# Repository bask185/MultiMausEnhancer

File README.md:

# MultiMausEnhancer, makes the roco multimaus more user friendly

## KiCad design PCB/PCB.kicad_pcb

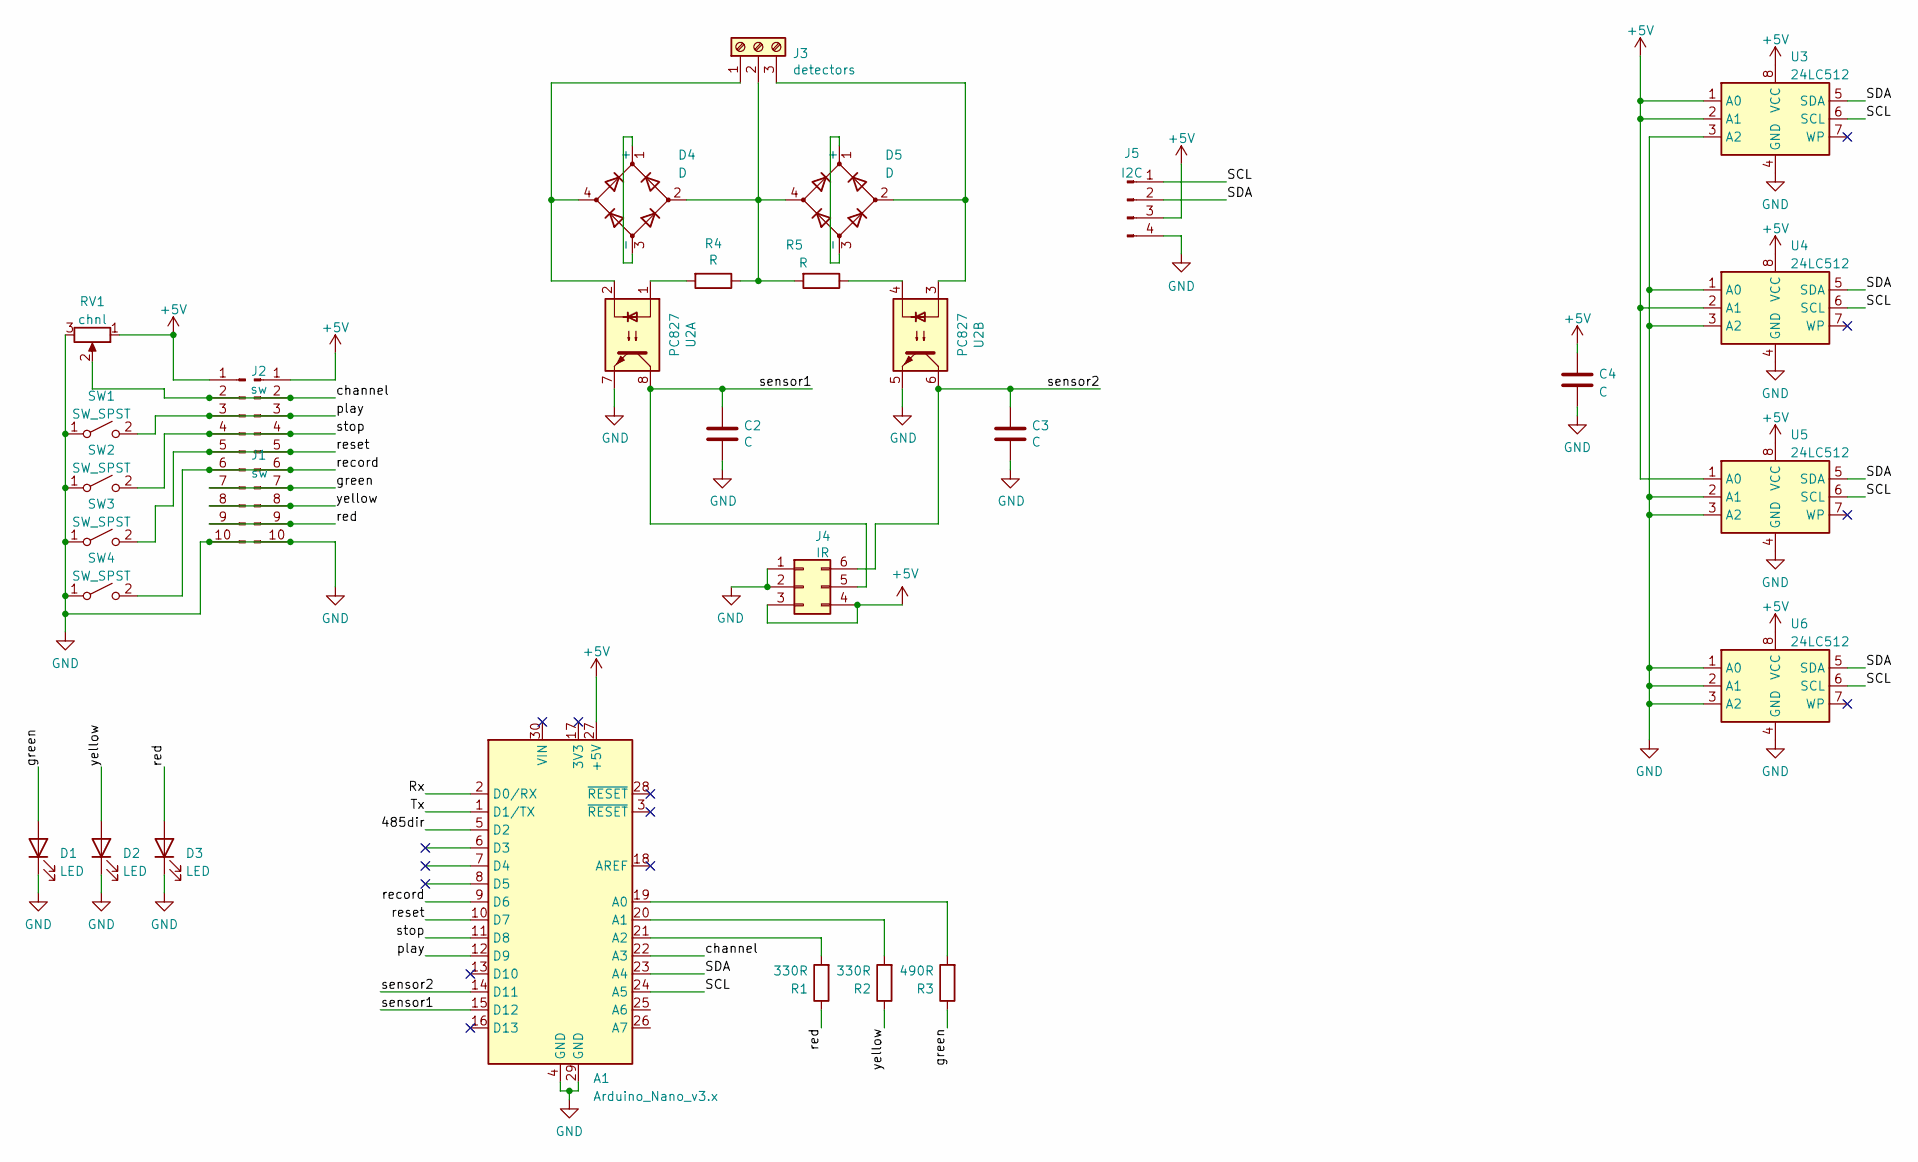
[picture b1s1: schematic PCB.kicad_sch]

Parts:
A1: Arduino_Nano_v3.x; Arduino_Nano
C2, C3, C4: C; C_Disc_D3.0mm_W1.6mm_P2.50mm
D1, D2, D3: LED; LED_D3.0mm
D4, D5: D; Diode_Bridge_Round_D9.0mm
J1, J2: sw; PinHeader_1x10_P2.54mm_Vertical
J3: detectors; TerminalBlock_Phoenix_MKDS-1,5-3-5.08_1x03_P5.08mm_Horizont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
J4: IR; PinHeader_2x03_P2.54mm_Vertical
J5: I2C; PinHeader_1x04_P2.54mm_Vertical
R1, R2: 330R; R_Axial_DIN0204_L3.6mm_D1.6mm_P7.62mm_Horizontal
R3: 490R; R_Axial_DIN0204_L3.6mm_D1.6mm_P7.62mm_Horizontal
R4, R5: R; R_Axial_DIN0204_L3.6mm_D1.6mm_P7.62mm_Horizontal
RV1: chnl; PinHeader_1x03_P2.54mm_Vertical
SW1, SW2, SW3, SW4: SW_SPST; SW_PUSH_6mm_H4.3mm
U2: PC827; DIP-8_W7.62mm
U3, U4, U5, U6: 24LC512; DIP-8_W7.62mm

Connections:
+5V: A1.27 (+5V), C4.1, J1.1, J2.1, J4.3, J4.4, J5.3, RV1.1, U3.1 (A0), U3.2 (A1), U3.8 (VCC), U4.2 (A1), U4.8 (VCC), U5.1 (A0), U5.8 (VCC), U6.8 (VCC)
/485dir: A1.5 (D2)
/Rx: A1.2 (D0/RX)
/SCL: A1.24 (A5), J5.1, U3.6 (SCL), U4.6 (SCL), U5.6 (SCL), U6.6 (SCL)
/SDA: A1.23 (A4), J5.2, U3.5 (SDA), U4.5 (SDA), U5.5 (SDA), U6.5 (SDA)
/Tx: A1.1 (D1/TX)
/channel: A1.22 (A3), J1.2, J2.2, RV1.2
/green: D1.2 (A), J1.7, J2.7, R3.1
/play: A1.12 (D9), J1.3, J2.3, SW1.2 (B)
/record: A1.9 (D6), J1.6, J2.6, SW4.2 (B)
/red: D3.2 (A), J1.9, J2.9, R1.1
/reset: A1.10 (D7), J1.5, J2.5, SW3.2 (B)
/sensor1: A1.15 (D12), C2.1, J4.5, U2.8
/sensor2: A1.14 (D11), C3.1, J4.6, U2.6
/stop: A1.11 (D8), J1.4, J2.4, SW2.2 (B)
/yellow: D2.2 (A), J1.8, J2.8, R2.1
GND: A1.4 (GND), A1.29 (GND), C2.2, C3.2, C4.2, D1.1 (K), D2.1 (K), D3.1 (K), J1.10, J2.10, J4.1, J4.2, J5.4, RV1.3, SW1.1 (A), SW2.1 (A), SW3.1 (A), SW4.1 (A), U2.5, U2.7, U3.3 (A2), U3.4 (GND), U4.1 (A0), U4.3 (A2), U4.4 (GND), U5.2 (A1), U5.3 (A2), U5.4 (GND), U6.1 (A0), U6.2 (A1), U6.3 (A2), U6.4 (GND)
unnamed: A1.19 (A0), R3.2
unnamed: A1.20 (A1), R2.2
unnamed: A1.21 (A2), R1.2
unnamed: D4.1 (+), D4.3 (-)
unnamed: D4.2, D5.4, J3.2, R4.1, R5.2
unnamed: D4.4, J3.1, U2.2
unnamed: D5.1 (+), D5.3 (-)
unnamed: D5.2, J3.3, U2.3
unnamed: R4.2, U2.1
unnamed: R5.1, U2.4

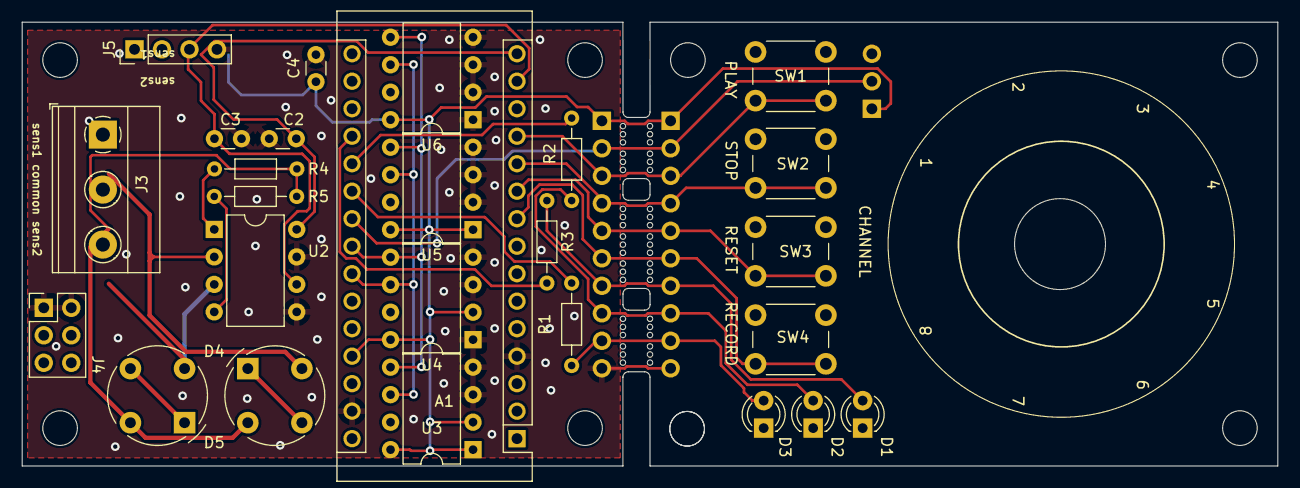
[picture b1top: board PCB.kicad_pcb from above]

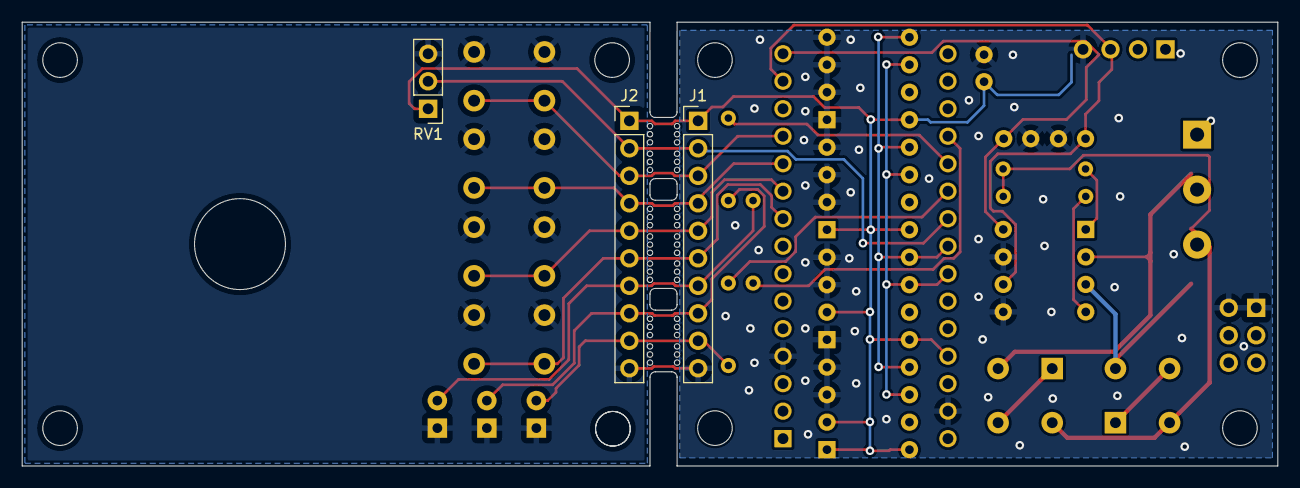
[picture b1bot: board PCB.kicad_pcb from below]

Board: 2 copper layers, 116.0 x 41.0 mm, 29 parts (3 on the bottom side), 24 nets.

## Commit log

2022-02-17 project has been made compilable. The function setPoint must be re-written
2022-02-17 added some code ready for testing
2022-02-19 this setup works for a large part. There are still some inconsisticies with the speed numbers
2022-02-20 first working setup, do need to add to remember the states of all points so one does not have to press twice to flip a point
2022-02-20 not yet entirely working. The 64 bit variable may not even work, this should be checked
2022-02-21 added new substitutes to better get the function numbers out of the xpressNet library
2022-02-21 made project compile-able
2022-02-21 some work done on point streets
2022-02-21 commit for push
2022-02-21 I can succesfully use a pseudo point address to set entire streets loaded from EEPROM. Now I must teachin the points
2022-02-22 function numbers have an improved toggle system for points, but it does not yet work perfectly. There are some points working some more debugging is required. Also the default state should be flipped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
2022-02-23 added eeprom files to manage point streets
2022-02-24 made a beginning with EEPROM storage
2022-02-25 made some drastic changes to point streets
2022-02-25 changed some minor things, did best to debug the notifytrnt function but once again, nothing seems to work
2022-02-25 arduino now keeps crashing, going to try older version
2022-03-01 This version is able to store points with input from the keyboard.
    The one thing I must fix is that the received street index must be -1 because the lower 32 bytes of EEPROM is not used.
    Regardless of this address shift, the code works well. Now to get it to work with a MM
2022-03-01 enabled the xpressnet library again and made project compilable with and without DEBUG
2022-03-10 Added working debug lighting module. Code works well with serial monitor. If I get the XpressNet notify function to work properly again, this code should work fine. This will be merged in the main br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
2022-03-10 somewhoe the .ino files was not in git?
2022-03-10 minor tweaks to event times
2022-03-10 force added IO files
2022-04-14 added debug method to use software serial. I must find out why the arduino crashes after setting or getting a point. This behaviour will die
2022-04-14 added more software serial debug messages
2022-04-18 renamed eeprom to points. Software works mostly. Toggling of the points does net yet work yet. About to add a shuttle service of some sort
2022-04-18 The first attempt with recording and playing a program has been succesfully tested using 4 accessory decoders! Next step is to try to move a train.
    There is one minor bug. If a program is started, it will repeat indefinatly which is good. However. If you stop and manually restart the program, it will no longer fire.
2022-04-19 replaced the event files by new ones which already work. They do need filling in and are currently commented out
    First I am going to add sensors for recording, followed by loco functions
2022-04-19 added function to the recording system. Yet to be tested
2022-04-19 added a prototype feedback method using pin 5 as sensor input. This will store feedback '123' into eeprom.
2022-04-19 fixed 2 minor bugs. For the first index of point streets. The lower bytes of EEPROM weren't used.
    There also was a -1 in the function setPoint. Which would cause one wrong point to be set and one right point not to be set
2022-04-19 code has been somewhat tested. Storing instructions for speed and functions seem to work well. But the arduino is somehow not allowed to send instructions on Xnet. I can see the functions being set a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
2022-04-20 some succes with feedback. I forgot how miserable the adress system was. Addresses needs to be fixed. First 8 are fine, other 8 aren't. Also found that the system would not restart because the interv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
    Also my Gnd DR4088 randomly died, and one of the inputs of the OPTO is dead.... FML...
    The program does correctly process feedback in both storing as well as playing. That part atleast works
2022-04-21 merged
2022-04-21 drastically refactored the entire event code. Shuttle.cpp and h are replaced by event.cpp and .h The event files are also made abstract. There are only 3 default events, start, stop and feedback. I b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
2022-04-21 added some code for testing feedback. The module addresses are most critical. If these are correct, all should be fine
2022-04-21 also made a change in the library where feedback is sent, this propably need more altering... but I do not yet full grasp how the library functions..
2022-04-22 made a minor tweak to the XpressNet library. Feeback addresses should not be modified at all.
2022-04-22 the points storing is still working on the z21 notify speed 28 and 128 are neither working. Stopping with recording seems too work.. but there is no message..
    I am also sure that the XpressNet library contains an address error somewhere with the feedback
2022-04-23 Code is operational using occupance detectors. I did some tweaking to the feedback addresses. I believe that only 4-8 modules will actually work and that there is still something which shoudln't be.
2022-04-23 # First working version using occupancy detectors. I suspect EEPROM is by far too little. The feedback addresses are also not yet what it should be but atleast 4-8 modules will work.. which should be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
2022-04-24 altered the event source codes with better starting playing.
2022-04-24 made an error in eventHandler where the feedback events were broken
2022-04-25 changed event.cpp and .h to be OOP. Also laid first stone for I2C eeprom. The new put and get methods are to be in their own files..
2022-04-25 event handler has been made OOP. Program compiles but is not tested
2022-04-25 made alteration. Both internal and i2c eeprom can be used. Begin address is configurable in the constrictor. Still need actual code for the I2C part, but that ain't no rocketscience
2022-04-25 added i2c eeprom files to project
2022-04-27 added first draught PCB files
2022-04-28 did routing of PCB design. I must investigate if I want an extra I2C port to be used with I2C to create extra buttons to this system
2022-04-28 added I2C connector on the side. Routing needs to be re done for a large part
2022-06-13 modified this program to work with the shuttle pcb. IO is working, recording and playing seems to work partially. Xnet functions are not yet entirely working, The yellow led also does not light up pr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
2022-06-14 added and updated event files. The event are updated with start recording, stop recording, start playing, stop playing and finishing
2022-06-14 added servo sweep library and commissioned the object. Project compiles and should work
2022-06-14 deleted the points files, not needed in this branch
2022-06-14 all is FUBAR. Once again XpressNet shit keeps crashing and I cant find anything to explain.
2022-06-30 added event and i2ceeprom files
